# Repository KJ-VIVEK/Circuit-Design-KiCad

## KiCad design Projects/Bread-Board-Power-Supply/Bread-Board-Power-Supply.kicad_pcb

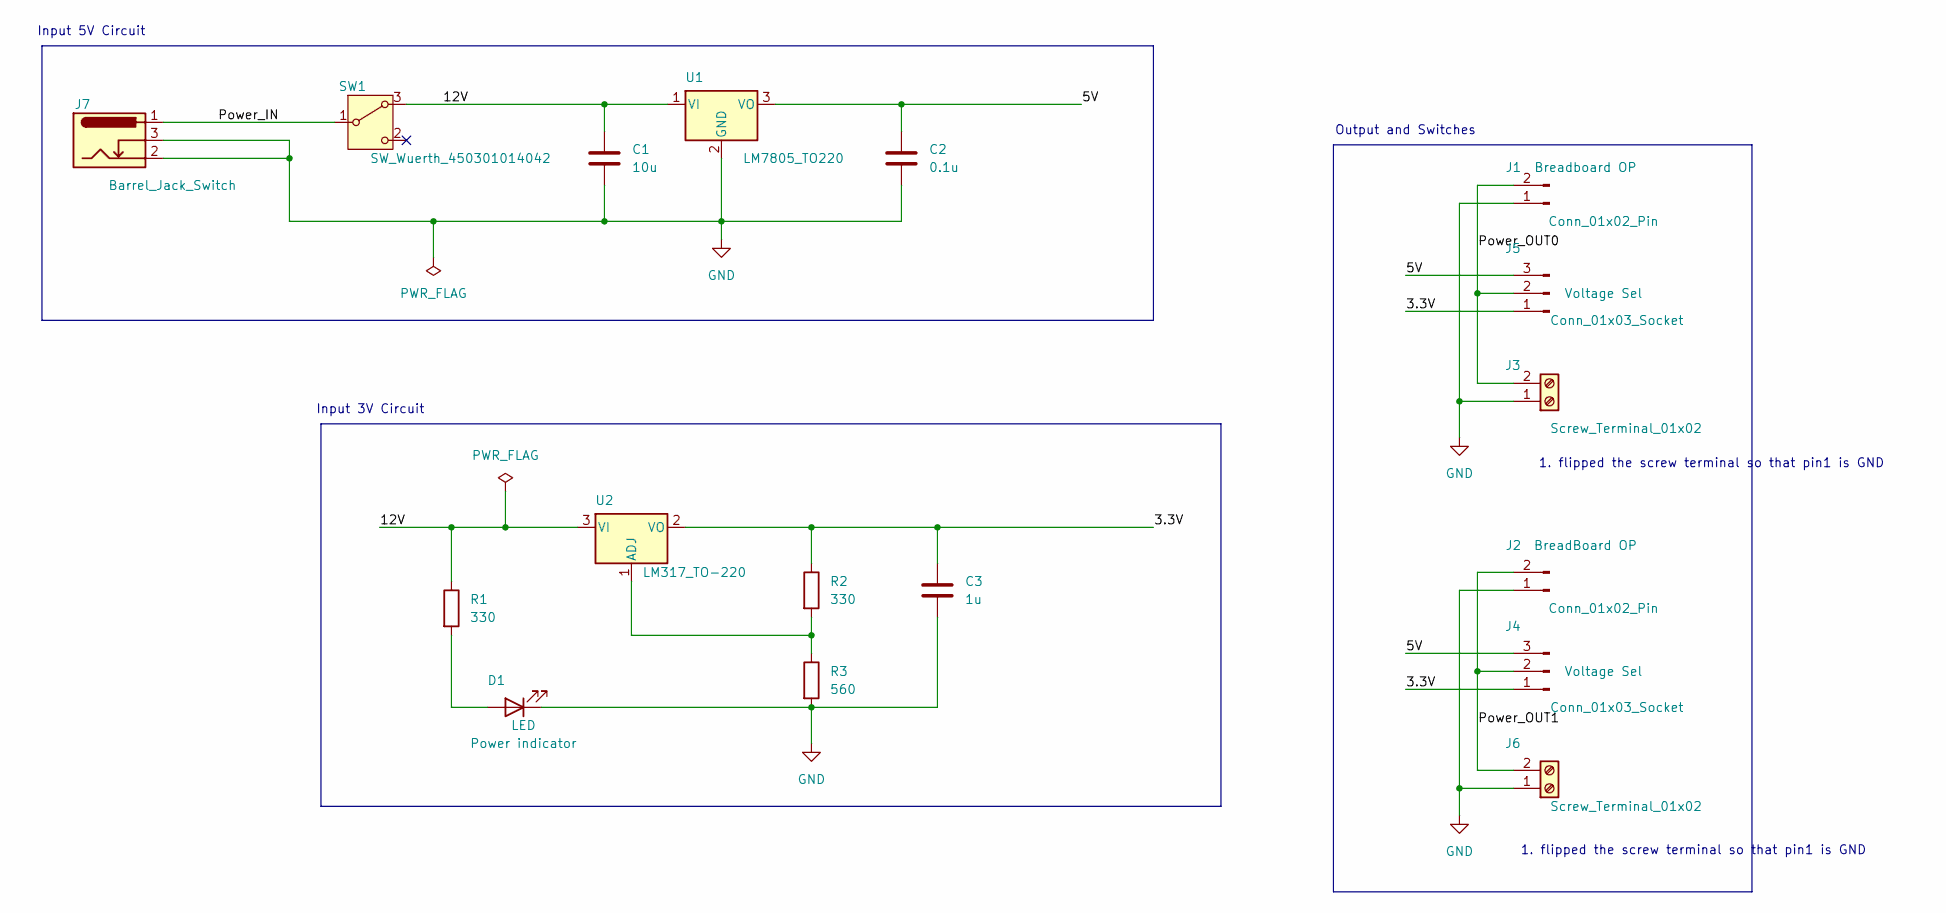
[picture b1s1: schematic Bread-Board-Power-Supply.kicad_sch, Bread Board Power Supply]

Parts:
C1: 10u; C_Disc_D3.0mm_W1.6mm_P2.50mm
C2: 0.1u; C_Disc_D3.0mm_W1.6mm_P2.50mm
C3: 1u; C_Disc_D3.0mm_W1.6mm_P2.50mm
D1: LED; LED_D5.0mm
J1, J2: Conn_01x02_Pin; PinHeader_1x02_P2.54mm_Vertical
J3, J6: Screw_Terminal_01x02; TerminalBlock_bornier-2_P5.08mm
J4, J5: Conn_01x03_Socket; PinHeader_1x03_P2.54mm_Vertical
J7: Barrel_Jack_Switch; BarrelJack_Horizontal
R1, R2: 330; R_Axial_DIN0204_L3.6mm_D1.6mm_P7.62mm_Horizontal
R3: 560; R_Axial_DIN0204_L3.6mm_D1.6mm_P7.62mm_Horizontal
SW1: SW_Wuerth_450301014042; SW_Slide-03_Wuerth-WS-SLTV_10x2.5x6.4_P2.54mm
U1: LM7805_TO220; TO-220-3_Vertical
U2: LM317_TO-220; TO-220-3_Vertical

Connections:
/3.3V: C3.1, J4.1, J5.1, R2.1, U2.2 (VO)
/5V: C2.1, J4.3, J5.3, U1.3 (VO)
/12V: C1.1, R1.1, SW1.3 (A), U1.1 (VI), U2.3 (VI)
/Power_IN: J7.1, SW1.1 (B)
/Power_OUT0: J1.2, J3.2, J5.2
/Power_OUT1: J2.2, J4.2, J6.2
GND: C1.2, C2.2, C3.2, D1.1 (K), J1.1, J2.1, J3.1, J6.1, J7.2, J7.3, R3.2, U1.2 (GND)
unnamed: D1.2 (A), R1.2
unnamed: R2.2, R3.1, U2.1 (ADJ)

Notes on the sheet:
Input 5V Circuit
1. flipped the screw terminal so that pin1 is GND
Input 3V Circuit
Output and Switches

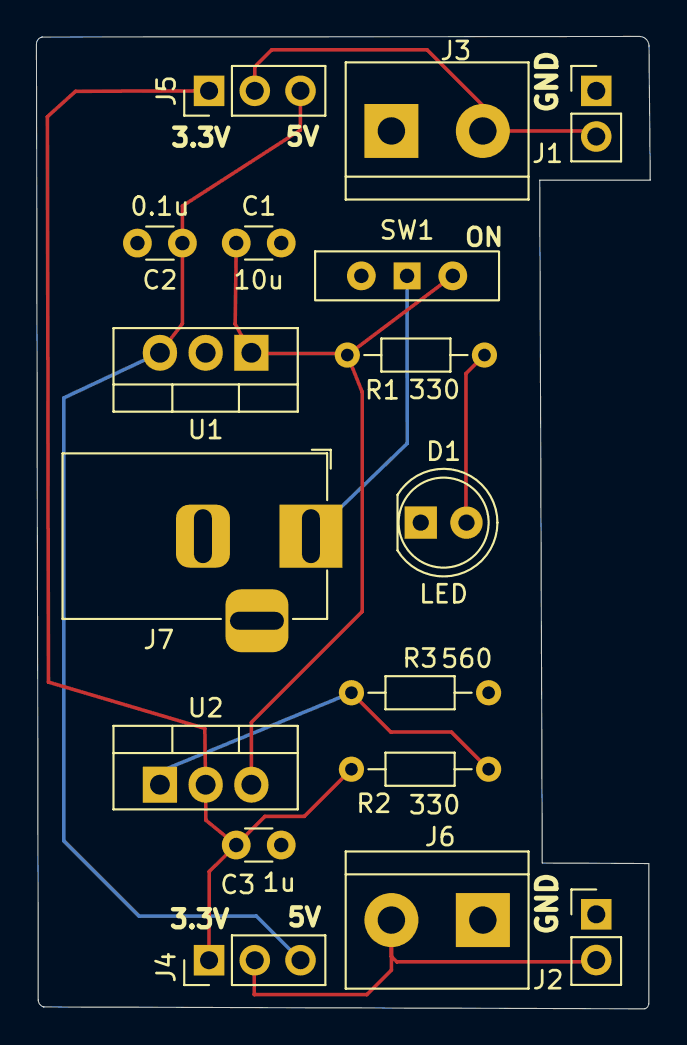
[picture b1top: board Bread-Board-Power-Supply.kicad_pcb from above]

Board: 2 copper layers, 34.1 x 54.0 mm, 17 parts (0 on the bottom side), 9 nets.

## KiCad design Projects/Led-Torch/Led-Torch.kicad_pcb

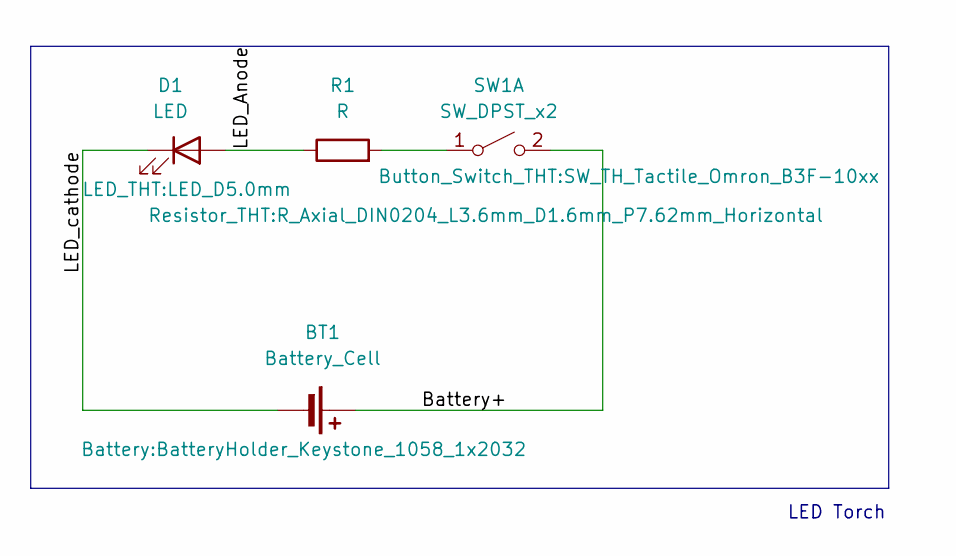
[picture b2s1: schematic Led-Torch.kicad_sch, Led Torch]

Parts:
BT1: Battery_Cell; BatteryHolder_Keystone_1058_1x2032
D1: LED; LED_D5.0mm
R1: R; R_Axial_DIN0204_L3.6mm_D1.6mm_P7.62mm_Horizontal
SW1: SW_DPST_x2; SW_TH_Tactile_Omron_B3F-10xx

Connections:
/Battery+: BT1.1 (+), SW1.2 (B)
/LED_Anode: D1.2 (A), R1.1
/LED_cathode: BT1.2 (-), D1.1 (K)
unnamed: R1.2, SW1.1 (A)

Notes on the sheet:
LED Torch

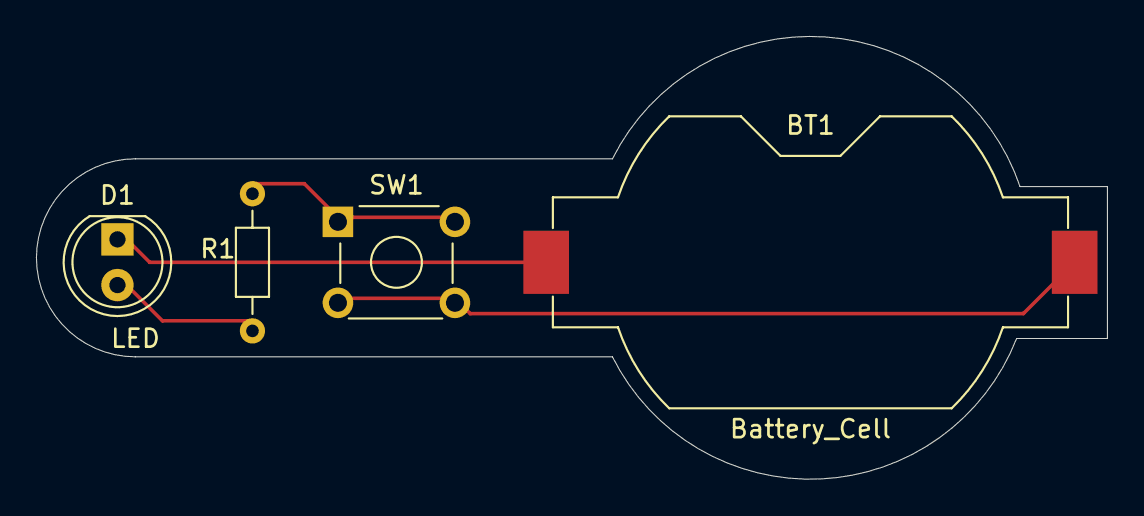
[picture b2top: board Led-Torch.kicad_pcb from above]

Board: 2 copper layers, 59.5 x 24.6 mm, 4 parts (0 on the bottom side), 4 nets.

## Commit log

2025-04-22 1. Initial folder setup. 2. Designing Led torch.
2025-04-23 proj-2: Designing powersuppply for bread board
